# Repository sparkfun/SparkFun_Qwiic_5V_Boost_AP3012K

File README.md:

SparkFun Qwiic 5V Boost - AP3012K
========================================

From its Qwiic connectors, the [SparkFun Qwiic 5V Boost - AP3012K](https://https://www.sparkfun.com/sparkfun-qwiic-5v-boost-ap3012k.html) converts the **3.3V** logic-level of the I<sup>2</sup>C signals and boosts the **3.3V** power supply; all to **5V** on its [PTH *(plated through-hole)*](https://en.wikipedia.org/wiki/Through-hole_technology) pins. This is handy for connecting any I<sup>2</sup>C device that requires a higher supply voltage for an RGB LED or mechanisms like a DC fan on our air quality sensors:

- [Sensirion SPS30 - Particulate Matter Sensor](https://www.sparkfun.com/particulate-matter-sensor-sps30.html)
- [Sensirion SEN54 - Particle, VOC, Humidity, and Temperature Sensor](https://www.sparkfun.com/particle-voc-humidity-and-temperature-sensor-sen54.html)
- [Sensirion SEN55 - Particle, VOC, NO<sub>x</sub>, Humidity, and Temperature Sensor](https://www.sparkfun.com/sensirion-particle-voc-humidity-and-temperature-sensor-sen55.html)

On the board, we provide `3V3`/`5V` jumpers, which can be used to configure the logic-levels of the I<sup>2</sup>C PTH pins. Therefore, this board can be utilized to connect an I<sup>2</sup>C device that requires any combination of 3.3V/5V for its power and/or signals. Additionally, the [TTL *(transistor–transistor logic)*](https://en.wikipedia.org/wiki/Transistor%E2%80%93transistor_logic) used to convert the logic-levels of the I<sup>2</sup>C signals can also implemented with other types of interfaces; such as a serial bus, similar to our [SparkFun Logic Level Converter - Single Supply](https://www.sparkfun.com/sparkfun-logic-level-converter-single-supply.html).

<hr>

> [!WARNING]
> Soldering is required to connect a 5V I<sup>2</sup>C device to this board.

> [!NOTE]
> The boost circuit on this board is rated to source up to a 100mA at 5V output, with 90% efficiency. However, users should note that this limitation is not only dependent on the load being connected, but also the amount of current that is being sourced to the Qwiic connector system.

Documentation
--------------
- **[Hookup Guide (mkdocs)](http://docs.sparkfun.com/SparkFun_Qwiic_5V_Boost_AP3012K/)** - A hookup guide for the Qwiic 5V Boost - AP3012K, hosted by GitHub pages.<br>

  *Need to download or print our hookup guide?*

  - [Print *(Print to PDF)* from Single-Page View](http://docs.sparkfun.com/SparkFun_Qwiic_5V_Boost_AP3012K/print_view)

Repository Contents
-------------------
- **[/docs](/docs/)** - Online documentation files
    - [/assets](/docs/assets/) - Assets files
        - [/3d_model](/docs/assets/3d_model/) - Files for the 3D models
            - [3D CAD Model](/docs/assets/3d_model/cad_model.step) (.step)
        - [/board_files](/docs/assets/board_files/) - Files for the product design
            - [KiCad Design Files](/docs/assets/board_files/kicad_files.zip) (.zip)
            - [Schematic](/docs/assets/board_files/schematic.pdf) (.pdf)
            - [Dimensions](/docs/assets/board_files/dimensions.pdf) (.pdf)
        - [/component_documentation](/docs/assets/component_documentation/) - Datasheets for hardware components
        - [/img/hookup_guide/](/docs/assets/img/hookup_guide/) - Images for hookup guide documentation
- **[/Hardware](/Hardware/)** - Hardware design files (.brd, .sch)
  - **[/Production](/Production/)** - Production files

Product Variants
----------------
- [PRT-28203](https://www.sparkfun.com/sparkfun-qwiic-5v-boost-ap3012k.html) - Initial Release

Version History
---------------
- [v10](https://github.com/sparkfun/SparkFun_Qwiic_5V_Boost_AP3012K/releases/tag/v10) - Initial Release

License Information
-------------------

This product is ***open source***!

Please review the [`LICENSE.md`](./LICENSE.md) file for license information.

If you have any questions or concerns about licensing, please contact technical support on our [SparkFun forums](https://community.sparkfun.com/).

Distributed as-is; no warranty is given.

- Your friends at SparkFun.

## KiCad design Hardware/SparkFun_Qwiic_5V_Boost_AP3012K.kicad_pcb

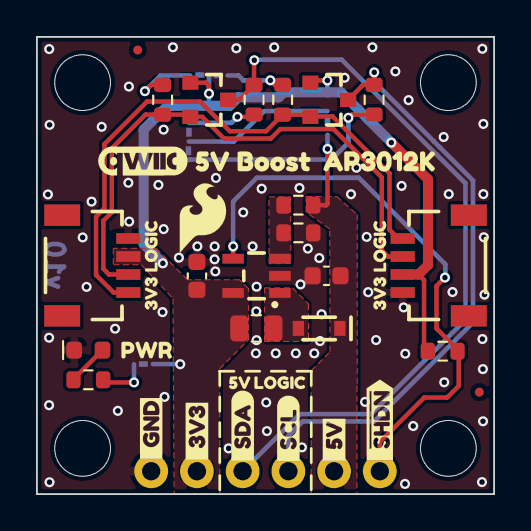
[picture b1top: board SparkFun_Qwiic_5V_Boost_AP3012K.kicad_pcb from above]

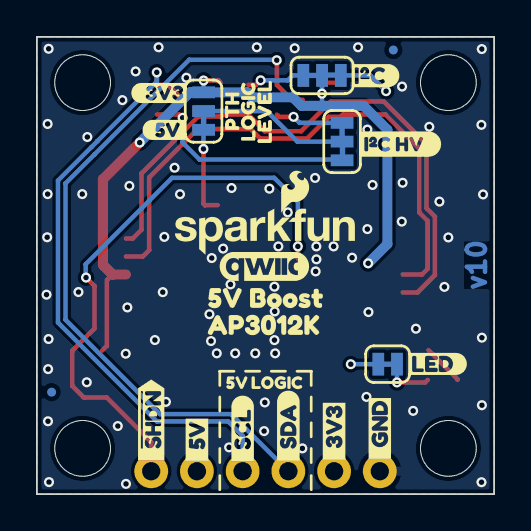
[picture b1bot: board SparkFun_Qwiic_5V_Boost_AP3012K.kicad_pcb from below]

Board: 2 copper layers, 25.4 x 25.4 mm, 63 parts (24 on the bottom side), 17 nets.

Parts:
C1, C2: 1.0uF; C_0603_1608Metric
D1: Red; LED_0603_1608Metric_Red
D2: PMEG4005EJ; SOD-323
FID1, FID2, FID3, FID4: Fiducial_0.5mm; Fiducial_0.5mm_Mask1mm
G4: OSHW_Logo; Creative_Commons_License
J1, J2: Qwiic_RA; JST_SMD_1.0mm-4_RA
J3: Conn_01x06; 1x06
JP1: LED; Jumper_2_NC_Trace
JP2: I2C; Jumper_3_NC-2_Trace
JP3: LOGIC; Jumper_3_NC-1_Trace
JP4: I2C HV; Jumper_3_NC-2_Trace
L1: 10uH; C_0805_2012Metric
Q1, Q2: BSS138; SOT23-3
R1, R6: 100k; R_0603_1608Metric
R2: 33k; R_0603_1608Metric
R3: 4.7k; R_0603_1608Metric
R4, R5, R7, R8: 2.2k; R_0603_1608Metric
ST1, ST2, ST3, ST4: Standoff
U5: AP3012; SOT23-5
kibuzzard-65A8A8B4: G***; kibuzzard-65A8A8B4
kibuzzard-65A8B05B: G***; kibuzzard-65A8B05B
kibuzzard-67A51B2D: G***; kibuzzard-67A51B2D
kibuzzard-67A51B3F: G***; kibuzzard-67A51B3F
kibuzzard-67A51B57: G***; kibuzzard-67A51B57
kibuzzard-67A51CFE, kibuzzard-67A51CFE#2: G***; kibuzzard-67A51CFE
kibuzzard-67A5195F: G***; kibuzzard-67A5195F
kibuzzard-67A51507, kibuzzard-67A51507#2: G***; kibuzzard-67A51507
kibuzzard-67AB7F1B: G***; kibuzzard-67AB7F1B
kibuzzard-67AB7F2D: G***; kibuzzard-67AB7F2D
kibuzzard-67BF5EEE, kibuzzard-67BF5EEE#2: G***; kibuzzard-67BF5EEE
kibuzzard-67BF5EF7, kibuzzard-67BF5EF7#2: G***; kibuzzard-67BF5EF7
kibuzzard-67BF5F1D, kibuzzard-67BF5F1D#2: G***; kibuzzard-67BF5F1D
kibuzzard-67BF7C99: G***; kibuzzard-67BF7C99
kibuzzard-67BF7CAB: G***; kibuzzard-67BF7CAB
kibuzzard-67BF7CFE: G***; kibuzzard-67BF7CFE
kibuzzard-67BF7D5E: G***; kibuzzard-67BF7D5E
kibuzzard-67BF7D12: G***; kibuzzard-67BF7D12
kibuzzard-67BF7D85: G***; kibuzzard-67BF7D85
kibuzzard-67BF7EBF: G***; kibuzzard-67BF7EBF
kibuzzard-67BF7ED9: G***; kibuzzard-67BF7ED9
kibuzzard-67BF7F2F: G***; kibuzzard-67BF7F2F
kibuzzard-67BF7F4D: G***; kibuzzard-67BF7F4D
kibuzzard-67BF7F7D: G***; kibuzzard-67BF7F7D
kibuzzard-67BF7F13: G***; kibuzzard-67BF7F13
kibuzzard-67C0A4F9: G***; kibuzzard-67C0A4F9

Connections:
3.3V: C1.1, J1.2, J2.2, J3.2, JP1.2 (B), JP2.2 (B), JP3.3 (C), L1.1, Q1.1 (G), Q2.1 (G), R6.2, U5.5 (IN)
5V: C2.1, D2.1 (K), J3.5, JP3.1 (A), R1.2
GND: C1.2, C2.2, D1.1 (K), J1.1, J2.1, J3.1, R2.2, U5.2 (GND)
HV_SCL: J3.4, Q1.3 (D), R8.2
HV_SDA: J3.3, Q2.3 (D), R7.2
unnamed: D1.2 (A), R3.1
unnamed: D2.2 (A), L1.2, U5.1 (SW)
unnamed: JP1.1 (A), R3.2
unnamed: JP2.1 (A), R5.1
unnamed: JP2.3 (C), R4.2
unnamed: JP4.1 (A), R7.1
unnamed: JP4.3 (C), R8.1
unnamed: R1.1, R2.1, U5.3 (FB)
SCL: J1.4, J2.4, Q1.2 (S), R5.2
SDA: J1.3, J2.3, Q2.2 (S), R4.1
VCC: JP3.2 (B), JP4.2 (B)
~SHDN: J3.6, R6.1, U5.4 (~SHDN)

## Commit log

2025-02-06 datasheet and EVB user guide
2025-02-06 layout work
2025-02-07 removing backup files and updating gitignore
2025-02-07 silk adjustments - add flame logo to top
2025-02-08 Remove Folders Not Being Used
2025-02-08 Initial Setup GitHub Pages
2025-02-08 Move Documents into assets folder
2025-02-10 checklist run eng
    -sch cleanup
    -changed red led bias resistor to 4.7k
    -adjusted thermal reliefs/spokes on power PTH headers (GND, 3V3, 5V)
    -wire stubs removed
    -dimensions added
2025-02-10 datasheet
2025-02-10 userguide
2025-02-13 design review changes part 1
    -changed silk for logic jumper to PTH LOGIC LEVEL
    -Added dashed lines around ADS/SCL PHT headers to show these logic levels are set by LOGIC jumper.
    -Changed Value of JP3 to LOGIC
    -un-bolded sch block title texts, switched to blue color
    -aligned PWR silk label with LED perfectly
2025-02-14 Review part 2
    -Update layer names
    -changed material to TG135
    -Centered (roughly) the board design in the frame
    -set my grid/drill origin points to bottom left corner of PCB edge cut (aka dimensional outline).
    -updated measures
2025-02-26 more design review feedback
    -SCH, changed all flags to inputs
    -BRD, re-routed HV I2C lines to avoid coupling with 3V3 trace
    -BRD, adjusted 5V and SHDN routing for less vias/more-direct
    -BRD, adjusted SDA/SCL routing away from right qwiic connector to provide more clearance from mask.
    -BRD, removed and moved GND vias to avoid bottom silk
    -BRD, scooted GND vias near SDA/SCL header pins to avoid bulging in the pours.
2025-02-26 silk update logic level labels
    -added 3v3 logic level labels to qwiic connectors
    -changed PTH header silk to show default 5V logic level
2025-02-26 buzzard label adjustments
    -extended left side spacing of PTH buzzard labels to 6mils
    -positioned them so they clear the PTH header plastic molding courtyard
    -snapped them all to a 6.25mils grid.
2025-02-26 moving parts onto 12.5mil grid
    -moved parts (except the boost circuit stuff) onto the 12.5 mil grid.
2025-02-27 I2C HV pullup jumper
    -added pullup jumper for I2C HV
    -Updated D2 to latest footprint
2025-02-27 final feedback
    -BRD - turned on all layers to visible
    -SCH - changed note about max current to 100mA
    -nudged SDA trace to remove a bump
2025-02-27 updated attribution and issue date
2025-02-27 added 2 test points
    -added test points for 3V3 logic level SDA/SCL
2025-04-01 Update Docs Template
    Update template for documentation
2025-04-01 Remove files
    Redundant - already relocated into /docs/assets/component_documentation directory
2025-04-02 Add design files and 3D models
2025-04-10 Update README.md add Banner
    Add banner image
    Use template
    Add product description
    Add product links and image
    Use banner for product image
2025-04-10 Initial Docs Draft
2025-04-10 Update README.md
    Fix links
2025-04-10 Add build workflow
2025-04-10 Deployed 821783e with MkDocs version: 1.6.1
2025-04-10 Change redirect
    Redirect to quick start guide instead
2025-04-10 Deployed 9ff356e with MkDocs version: 1.6.1

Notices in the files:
parts and their libraries:
https://creativecommons.org/licenses/by-sa/4.0
Released under the Creative Commons Attribution Share-Alike 4.0 License
